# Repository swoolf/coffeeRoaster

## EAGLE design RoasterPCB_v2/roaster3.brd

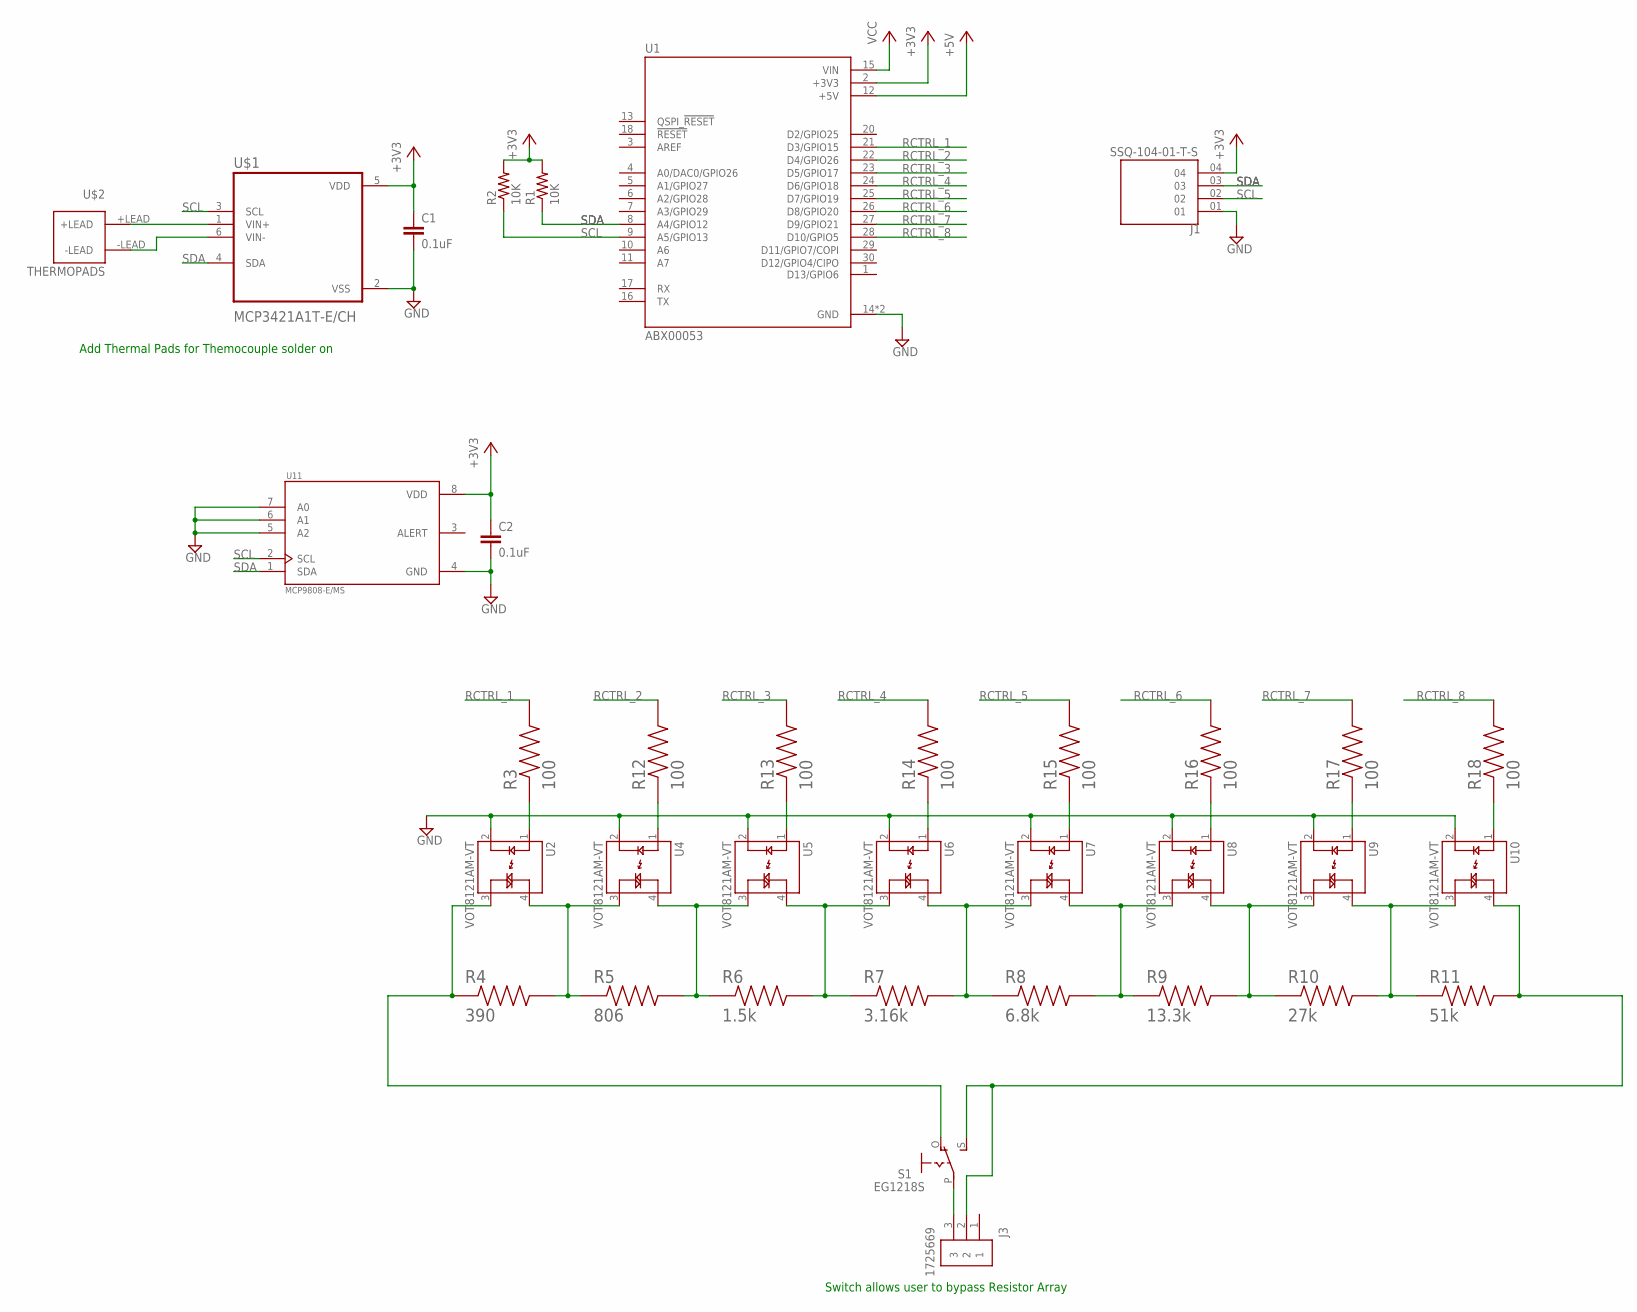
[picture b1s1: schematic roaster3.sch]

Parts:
C1, C2: 0.1uF; RUNJUMP_C0603
J1: SSQ-104-01-T-S; SAMTEC_SSQ-104-01-T-S
J3: 1725669; PHOENIX_1725669
R1, R2: 10K; RUNJUMP_R0603
R3, R12, R13, R14, R15, R16, R17, R18: 100; RESC1608X55N
R4: 390; RESC6332X70N
R5: 806; RESC6332X70N
R6: 1.5k; RESC6332X70N
R7: 3.16k; RESC6332X70N
R8: 6.8k; RESC6332X70N
R9: 13.3k; RESC6332X70N
R10: 27k; RESC6332X70N
R11: 51k; RESC6332X70N
S1: EG1218S; EG1218
U1: ABX00053; MODULE_ABX00053
U2, U4, U5, U6, U7, U8, U9, U10: VOT8121AM-VT; SOIC254P675X240-4N
U11: MCP9808-E/MS; SOP65P490X110-8N
U$1: MCP3421A1T-E/CH; SOT95P280X145-6N
U$2: THERMOPADS

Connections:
+3V3: C1.1, C2.1, J1.04, R1.2, R2.2, U1.2 (+3V3), U11.8 (VDD), U$1.5 (VDD)
+5V: U1.12 (+5V)
GND: C1.2, C2.2, J1.01, U1.14 (GND), U1.19 (GND), U2.2 (C), U4.2 (C), U5.2 (C), U6.2 (C), U7.2 (C), U8.2 (C), U9.2 (C), U10.2 (C), U11.4 (GND), U11.5 (A2), U11.6 (A1), U11.7 (A0), U$1.2 (VSS)
unnamed: J3.3, S1.P
unnamed: U$1.6 (VIN-), U$2.-LEAD
unnamed: U$1.1 (VIN+), U$2.+LEAD
unnamed: R5.2, R6.1, U4.4 (MT2), U5.3 (MT1)
unnamed: R4.1, S1.O, U2.3 (MT1)
unnamed: R4.2, R5.1, U2.4 (MT2), U4.3 (MT1)
unnamed: J3.2, R11.2, S1.S, U10.4 (MT2)
unnamed: R6.2, R7.1, U5.4 (MT2), U6.3 (MT1)
unnamed: R7.2, R8.1, U6.4 (MT2), U7.3 (MT1)
unnamed: R8.2, R9.1, U7.4 (MT2), U8.3 (MT1)
unnamed: R9.2, R10.1, U8.4 (MT2), U9.3 (MT1)
unnamed: R10.2, R11.1, U9.4 (MT2), U10.3 (MT1)
unnamed: R3.1, U2.1 (A)
unnamed: R12.1, U4.1 (A)
unnamed: R13.1, U5.1 (A)
unnamed: R14.1, U6.1 (A)
unnamed: R15.1, U7.1 (A)
unnamed: R16.1, U8.1 (A)
unnamed: R17.1, U9.1 (A)
unnamed: R18.1, U10.1 (A)
RCTRL_1: R3.2, U1.21 (D3/GPIO15)
RCTRL_2: R12.2, U1.22 (D4/GPIO26)
RCTRL_3: R13.2, U1.23 (D5/GPIO17)
RCTRL_4: R14.2, U1.24 (D6/GPIO18)
RCTRL_5: R15.2, U1.25 (D7/GPIO19)
RCTRL_6: R16.2, U1.26 (D8/GPIO20)
RCTRL_7: R17.2, U1.27 (D9/GPIO21)
RCTRL_8: R18.2, U1.28 (D10/GPIO5)
SCL: J1.02, R2.1, U1.9 (A5/GPIO13), U11.2 (SCL), U$1.3 (SCL)
SDA: J1.03, R1.1, U1.8 (A4/GPIO12), U11.1 (SDA), U$1.4 (SDA)
VCC: U1.15 (VIN)

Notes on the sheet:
Add Thermal Pads for Themocouple solder on
Switch allows user to bypass Resistor Array

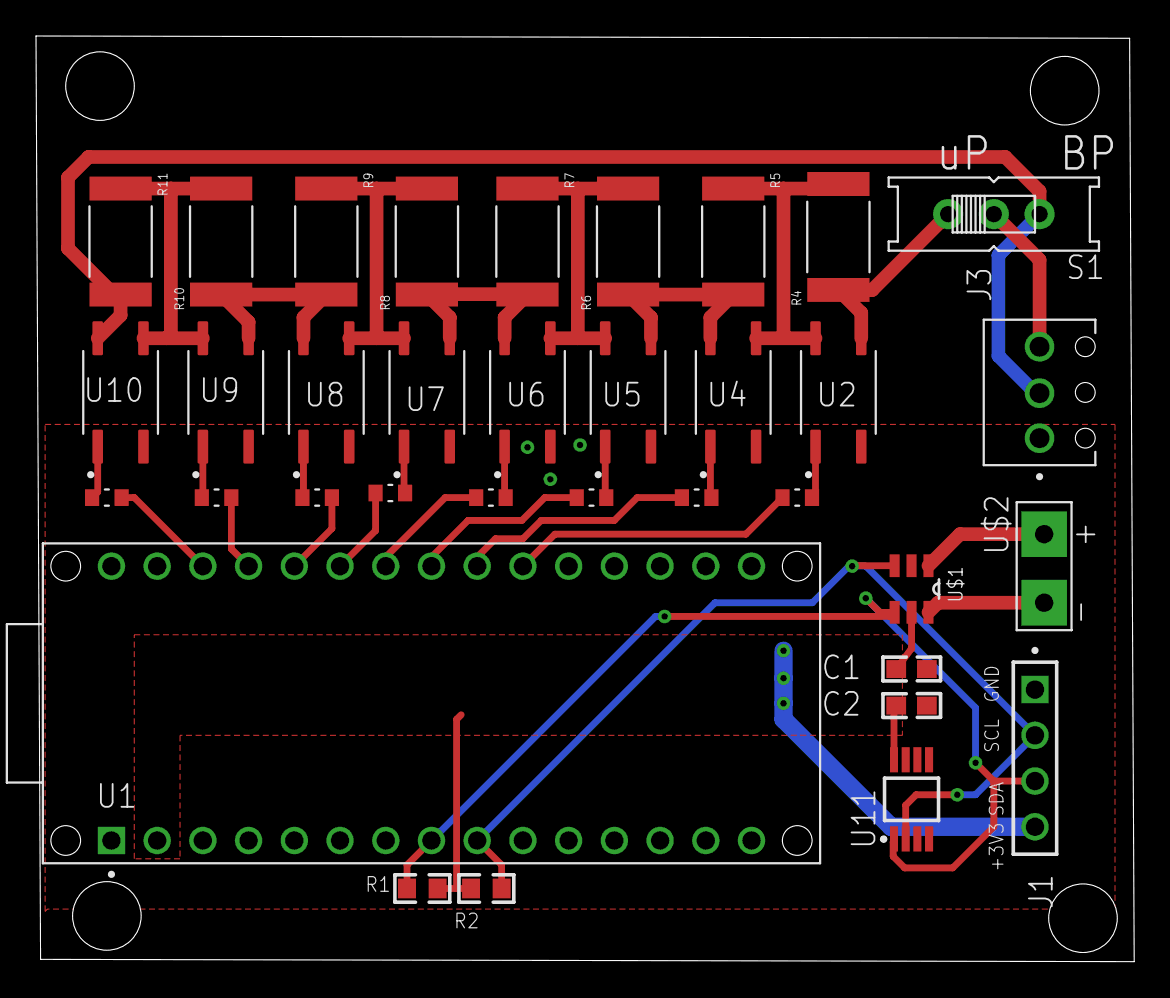
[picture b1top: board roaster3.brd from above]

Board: 2 copper layers, 61.0 x 51.4 mm, 35 parts (0 on the bottom side), 32 nets.

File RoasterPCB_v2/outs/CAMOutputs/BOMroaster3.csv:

"Qty";"Value";"Device";"Package";"Parts";"Description";"AVAILABILITY";"DESCRIPTION";"DIGI-KEY_PART_NUMBER";"DIGIKEY_PN";"MF";"MFR";"MFR_PN";"MP";"PACKAGE";"PN_DIGIKEY";"POWER";"PRICE";"PURCHASE-URL";"TOLERANCE";"URL_DIGIKEY";"VALUE";"VOLTAGE";
"2";"0.1uF";"RUNJUMP_CAPACITOR-0.1UF-DECOUPLING-0603";"RUNJUMP_C0603";"C1, C2";"Capacitor 0805";"";"";"";"";"";"Samsung Electro-Mechanics";"CL10A104KA8NNNC";"";"";"1276-1857-1-ND";"";"";"";"";"https://www.digikey.com/product-detail/en/samsung-electro-me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";"0.1uF";"25V";
"1";"1.5k";"RMCF2512JT1K50";"RESC6332X70N";"R6";"Check availability";"";"1.5k ohms";"";"RMCF2512JT1K50";"Stackpole Electronics Inc";"";"";"";"";"";"";"";"";"";"";"1.5k";"";
"8";"100";"AC0603FR-10100RL";"RESC1608X55N";"R3, R12, R13, R14, R15, R16, R17, R18";"RES SMD 1.6M OHM 5% 1/10W 0603                                                                                                                                                                                                                                                                                                                                                                                                                                                                                                                                                    Check availability";"In Stock";" 100 Ohms ±1% 0.1W, 1/10W Chip Resistor 0603 (1608 Metric) Automotive AEC-Q200 Thick Film ";"";"AC0603FR-10100RL";"Yageo";"";"";"AC0603FR-10100RL";"None";"";"";"None";"https://pricing.snapeda.com/search/part/AC0603FR-10100RL/?ref=eda";"";"";"100";"";
"2";"10K";"RUNJUMP_RESISTOR-10K";"RUNJUMP_R0603";"R1, R2";"";"";"";"";"";"";"Samsung Electro-Mechanics";"RC1608J103CS";"";"";"1276-5086-1-ND";"";"";"";"5%";"https://www.digikey.com/product-detail/en/samsung-electro-me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";"10K";"";
"1";"13.3k";"RMCF2512FT13K3";"RESC6332X70N";"R9";"Check availability";"";"13.3kOhms";"";"RMCF2512FT13K3";"Stackpole Electronics Inc";"";"";"";"";"";"";"";"";"";"";"13.3k";"";
"1";"1725669";"1725669";"PHOENIX_1725669";"J3";"3 Position Wire to Board Terminal Block Horizontal with Board 0.100" (2.54mm) Through Hole Check availability";"In Stock";" 3 Position Wire to Board Terminal Block Horizontal with Board 0.100 (2.54mm) Through Hole ";"";"1725669";"Phoenix Contact";"";"";"1725669";"None";"";"";"None";"https://pricing.snapeda.com/search/part/1725669/?ref=eda";"";"";"";"";
"1";"27k";"RMCF2512JT27K0";"RESC6332X70N";"R10";"Check availability";"";"27kOhms";"";"RMCF2512JT27K0";"Stackpole Electronics Inc";"";"";"";"";"";"";"";"";"";"";"27k";"";
"1";"3.16k";"RMCF2512FT3K16";"RESC6332X70N";"R7";"Check availability";"";"3.16kOhms";"";"RMCF2512FT3K16";"Stackpole Electronics Inc";"";"";"";"";"";"";"";"";"";"";"3.16k";"";
"1";"390";"RMCF2512JT390R";"RESC6332X70N";"R4";"Check availability";"In Stock";" 390 Ohms ±5% 1W Chip Resistor 2512 (6432 Metric) Automotive AEC-Q200 Thick Film ";"";"RMCF2512JT390RCT-ND";"Stackpole Electronics Inc";"";"";"RMCF2512JT390R";"6332 Stackpole";"";"";"None";"https://pricing.snapeda.com/search/part/RMCF2512JT390R/?ref=eda";"";"";"390";"";
"1";"51k";"RMCF2512JT51K0";"RESC6332X70N";"R11";"Check availability";"";"51kohms";"";"RMCF2512JT51K0";"Stackpole Electronics Inc";"";"";"";"";"";"";"";"";"";"";"51k";"";
"1";"6.8k";"RMCF2512JT6K80";"RESC6332X70N";"R8";"Check availability";"";"6.8kOhms";"";"RMCF2512JT6K80";"Stackpole Electronics Inc";"";"";"";"";"";"";"";"";"";"";"6.8k";"";
"1";"806";"RMCF2512FT806R";"RESC6332X70N";"R5";"";"";"";"";"RMCF2512FT806RCT-ND ";"";"";"";"";"";"";"";"";"";"";"";"806";"";
"1";"ABX00053";"ABX00053";"MODULE_ABX00053";"U1";"ARDUINO NANO RP2040 CONNECT WITH";"";" NINA-W102, RP2040 Arduino Nano RP2040 Connect with Headers series ARM® Cortex®-M0+ MCU 32-Bit Embedded Evaluation Board ";"1050-ABX00053-ND";"";"Arduino";"";"";"ABX00053";"None";"";"";"";"https://pricing.snapeda.com/search/part/ABX00053/?ref=eda";"";"";"";"";
"1";"EG1218S";"EG1218S";"EG1218";"S1";"SLIDING SWITCH";"In Stock";" SLIDE SWITCH, SPDT, 200MA";" Contact Configuration:SPDT";" Switch Operation:-";" Switch Mounting:Through Hole";" Product Range:-";" Contact Current Max:-";" Contact Voltage AC Max:-";" Contact Voltage DC Max:-";" Orientation:Vertical ";"";"EG1218.";"E-Switch";"";"";"EG1218.";"None";
"1";"MCP3421A1T-E/CH";"MCP3421A1T-E/CH";"SOT95P280X145-6N";"U$1";"Check availability";"In Stock";" 18 Bit Analog to Digital Converter 1 Input 1 Sigma-Delta SOT-23-6 ";"";"MCP3421A1T-E/CH";"Microchip Technology";"";"";"MCP3421A1T-E/CH";"SOT-23-6 Microchip";"";"";"None";"https://pricing.snapeda.com/search/part/MCP3421A1T-E/CH/?ref=eda";"";"";"";"";
"1";"MCP9808-E/MS";"MCP9808-E/MS";"SOP65P490X110-8N";"U11";"Board Mount Temperature Sensors Silicon temp sensor with I2C interface Check availability";"In Stock";" Temperature Sensor Digital, Local -40°C ~ 125°C 12 b 8-MSOP ";"";"MCP9808-E/MS";"Microchip";"";"";"MCP9808-E/MS";"MSOP-8 Microchip";"";"";"None";"https://pricing.snapeda.com/search/part/MCP9808-E/MS/?ref=eda";"";"";"";"";
"1";"SSQ-104-01-T-S";"SSQ-104-01-T-S";"SAMTEC_SSQ-104-01-T-S";"J1";"Check availability";"In Stock";" SSQ - Samtec 2.54mm Square Tail Single Row Socket Strip 8.5mm Profile - Fast Stock ";"";"SSQ-104-01-T-S";"Samtec Inc.";"";"";"SSQ-104-01-T-S";"None";"";"";"None";"https://pricing.snapeda.com/search/part/SSQ-104-01-T-S/?ref=eda";"";"";"";"";
"1";"THERMOPADS";"THERMOPADS";"THERMOPADS";"U$2";"";"";"";"";"";"";"";"";"";"";"";"";"";"";"";"";"";"";
"8";"VOT8121AM-VT";"VOT8121AM-VT";"SOIC254P675X240-4N";"U2, U4, U5, U6, U7, U8, U9, U10";"VOT8121AM-VT Check availability";"In Stock";" Optoisolator Triac Output 3750Vrms 1 Channel 4-SOP ";"";"VOT8121AM-VT";"Vishay Semiconductor Opto Division";"";"";"VOT8121AM-VT";"SMD-4 Vishay Semiconductor Opto Division";"";"";"None";"https://pricing.snapeda.com/search/part/VOT8121AM-VT/?ref=eda";"";"";"";"";

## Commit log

2024-02-26 First
